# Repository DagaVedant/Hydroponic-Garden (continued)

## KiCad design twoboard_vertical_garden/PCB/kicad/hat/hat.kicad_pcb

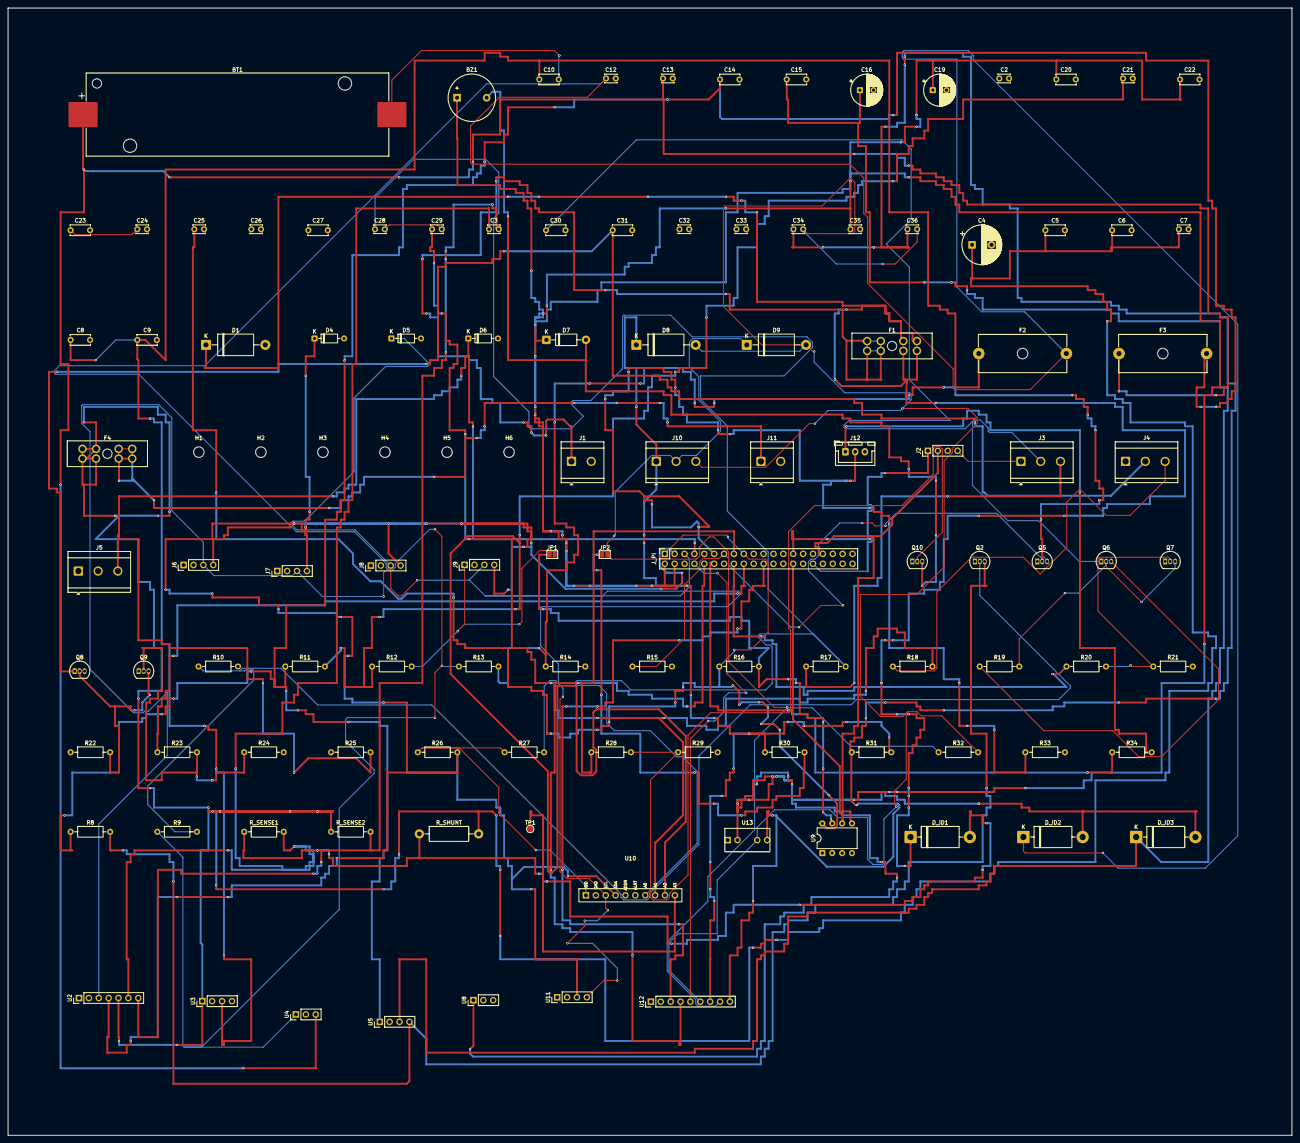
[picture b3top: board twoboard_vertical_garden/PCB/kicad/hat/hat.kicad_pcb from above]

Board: 4 copper layers, 330.0 x 289.7 mm, 117 parts (0 on the bottom side), 56 nets.

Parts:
BT1: 18650 protected; BatteryHolder_Keystone_1042_1x18650
BZ1: active 5V; Buzzer_12x9.5RM7.6
C2, C3, C7, C21, C24, C25, C26, C28, C29, C32, C33, C34: 100n; C_Disc_D3.0mm_W2.0mm_P2.50mm
C4: 470u 25V; CP_Radial_D10.0mm_P5.00mm
C5, C6: 10u 25V; C_Disc_D5.0mm_W2.5mm_P5.00mm
C8, C9, C10, C14, C15, C20, C23: 22u 10V; C_Disc_D5.0mm_W2.5mm_P5.00mm
C12, C13, C35, C36: 4u7; C_Disc_D3.0mm_W2.0mm_P2.50mm
C16: 220u 10V; CP_Radial_D8.0mm_P3.50mm
C19: 470u 10V; CP_Radial_D8.0mm_P3.50mm
C22, C27, C30, C31: 10u; C_Disc_D5.0mm_W2.5mm_P5.00mm
D1: SMBJ15A; D_DO-201AE_P15.24mm_Horizontal
D4, D5, D6: SMF5.0A; D_DO-35_SOD27_P7.62mm_Horizontal
D7: SS14; D_DO-41_SOD81_P10.16mm_Horizontal
D8, D9: SMAJ6.5CA; D_DO-201AE_P15.24mm_Horizontal
D_ID1, D_ID2, D_ID3: SB5H100; D_DO-201AD_P15.24mm_Horizontal
F1: 10A blade; FuseHolder_Blade_ATO_Littelfuse_FLR_178.6165
F2, F3: 3A; Fuseholder_Cylinder-5x20mm_Schurter_0031_8201_Horizontal_Op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
F4: 7.5A blade; FuseHolder_Blade_ATO_Littelfuse_FLR_178.6165
H1, H2, H3, H4, H5, H6: M2.5; MountingHole_2.7mm_M2.5
J1: 12V IN; TerminalBlock_CUI_TB007-508-02_1x02_P5.08mm_Horizontal
J2: spare gpio; PinHeader_1x04_P2.54mm_Vertical
J3: pH board; Gravity_TB3
J4: EC board; Gravity_TB3
J5: DS18B20; TerminalBlock_CUI_TB007-508-03_1x03_P5.08mm_Horizontal
J6: sht31 module; PinHeader_1x04_P2.54mm_Vertical
J7: veml7700 module; PinHeader_1x04_P2.54mm_Vertical
J8: scd40 module; PinHeader_1x04_P2.54mm_Vertical
J9: oled ssd1306; PinHeader_1x04_P2.54mm_Vertical
J10: RS485 A B G; TerminalBlock_CUI_TB007-508-03_1x03_P5.08mm_Horizontal
J11: 12V OUT; TerminalBlock_CUI_TB007-508-02_1x02_P5.08mm_Horizontal
J12: HB FLT GND; JST_XH_B3B-XH-A_1x03_P2.50mm_Vertical
JP1: WP; SolderJumper-2_P1.3mm_Open_Pad1.0x1.5mm
JP2: term; SolderJumper-2_P1.3mm_Open_Pad1.0x1.5mm
J_PI: Pi 40 pin; PinSocket_2x20_P2.54mm_Vertical
Q2, Q5, Q7, Q9, Q10: 2N7002; TO-92_Inline
Q6, Q8: AO3401A; TO-92_Inline
R8, R9, R10, R11, R12, R13, R14, R21, R24, R29: 100k; R_Axial_DIN0207_L6.3mm_D2.5mm_P10.16mm_Horizontal
R15, R16, R19, R22, R33: 10k; R_Axial_DIN0207_L6.3mm_D2.5mm_P10.16mm_Horizontal
R17, R18, R20, R23, R28: 1k; R_Axial_DIN0207_L6.3mm_D2.5mm_P10.16mm_Horizontal
R25: 4k7; R_Axial_DIN0207_L6.3mm_D2.5mm_P10.16mm_Horizontal
R26, R27: 2k2; R_Axial_DIN0207_L6.3mm_D2.5mm_P10.16mm_Horizontal
R30: 120R; R_Axial_DIN0207_L6.3mm_D2.5mm_P10.16mm_Horizontal
R31, R32: 47k; R_Axial_DIN0207_L6.3mm_D2.5mm_P10.16mm_Horizontal
R34: 100R; R_Axial_DIN0207_L6.3mm_D2.5mm_P10.16mm_Horizontal
R_SENSE1, R_SENSE2: 10R; R_Axial_DIN0207_L6.3mm_D2.5mm_P10.16mm_Horizontal
R_SHUNT: 5m 2512; R_Axial_DIN0411_L9.9mm_D3.6mm_P15.24mm_Horizontal
TP1: AIN3; TestPoint_Pad_D1.5mm
U2: INA226 module 0x40; PinHeader_1x07_P2.54mm_Vertical
U3: buck module 12V->5V; PinHeader_1x04_P2.54mm_Vertical
U4: li-ion charger module (500mA); PinHeader_1x03_P2.54mm_Vertical
U5: XL6009 boost module (VBAT_F->5V); PinHeader_1x04_P2.54mm_Vertical
U8: AMS1117 3.3V module; PinHeader_1x03_P2.54mm_Vertical
U9: 24LC32A; DIP-8_W7.62mm
U10: ADS1115 module; ADS1115_Module
U11: DS3231 RTC module; PinHeader_1x04_P2.54mm_Vertical
U12: isolated RS485 module; PinHeader_1x09_P2.54mm_Vertical
U13: B0505S-1WR3; B0505S_SIP4

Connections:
12V_FUSED: D1.1, D_ID1.1, F1.2
+3V3: C2.1, C23.1, C24.1, C26.1, C27.1, C32.1, C33.1, J2.3, J5.1, J6.1, J7.1, J8.1, J9.2, Q6.3, Q8.3, R15.2, R19.1, R22.1, R25.1, R26.1, R27.1, R33.2, U2.2, U8.3, U10.8, U11.1, U12.1
+3V3_PI: C25.1, J_PI.1, J_PI.17, R16.1, U9.8
+5V: BZ1.1, C19.1, C20.1, C22.1, C35.1, D7.1, D_ID2.2, D_ID3.2, J_PI.2, J_PI.4, U8.1, U13.2
+5VISO: C34.1, C36.1, R31.1, U12.9, U13.4
+5V_BAT: C15.1, C16.1, D_ID3.1, U5.3
+5V_IN: C8.1, C9.1, C10.1, F2.1, U3.3
+5V_MAINS: C12.1, D_ID2.1, F2.2, R9.1, R13.1, U4.1
+12V: C4.1, C5.1, C6.1, C7.1, F4.1, R_SENSE2.1, R_SHUNT.2, U2.5, U3.1
+12V_IN: F1.1, J1.1
/12V_DIODE: D_ID1.2, R_SENSE1.1, R_SHUNT.1
/AIN3: TP1.1, U10.7
/BUZZ: J_PI.15, R28.1
/EC_ADC: C29.1, R18.2, U10.5
/EC_EN: J_PI.18, R23.1
/FLT: J12.2, J_PI.11, R33.1
/HB: J_PI.12, R34.1
/INA_INP: C3.1, R_SENSE1.2, U2.6
/MAINS_N: J_PI.13, Q5.3, R15.1
/PH_ADC: C28.1, R17.2, U10.4
/PH_EN: J_PI.16, R20.1
/RS485_DE: J_PI.22, U12.3
/RS485_RX: J_PI.10, U12.4
/RS485_TX: J_PI.8, U12.5
/SCL: D5.1, J6.3, J7.3, J8.3, J9.3, J_PI.5, R27.2, U2.3, U10.10, U11.4
/SDA: D4.1, J6.4, J7.4, J8.4, J9.4, J_PI.3, R26.2, U2.4, U10.9, U11.3
/VBAT_SENSE: C21.1, R11.2, R12.1, U10.6
/W1: D6.1, J5.3, J_PI.7, R25.2
EC_VCC: C31.1, J4.1, Q8.1
GND: BT1.2, C2.2, C4.2, C5.2, C6.2, C7.2, C8.2, C9.2, C10.2, C12.2, C13.2, C14.2, C15.2, C16.2, C19.2, C20.2, C21.2, C22.2, C23.2, C24.2, C25.2, C26.2, C27.2, C28.2, C29.2, C30.2, C31.2, C32.2, C33.2, C35.2, D1.2, D4.2, D5.2, D6.2, J1.2, J2.4, J3.2, J4.2, J5.2, J6.2, J7.2, J8.2, J9.1, J11.2, J12.3, JP1.2, J_PI.6, J_PI.9, J_PI.14, J_PI.20, J_PI.25, J_PI.30, J_PI.34, J_PI.39, Q2.1, Q5.1, Q7.1, Q9.1, Q10.1, R10.2, R12.2, R14.2, R21.2, R24.2, R29.2, U2.1, U3.2, U3.4, U4.2, U5.2, U8.2, U9.1, U9.2, U9.3, U9.4, U10.1, U10.3, U11.2, U12.2, U13.1
GNDISO: C34.2, C36.2, D8.2, D9.2, J10.3, R32.2, U12.6, U13.3
unnamed: BZ1.2, D7.2, Q10.3
unnamed: D8.1, J10.1, R30.1, R31.2, U12.7
unnamed: D9.1, J10.2, JP2.2, R32.1, U12.8
unnamed: J2.1, J_PI.32
unnamed: J2.2, J_PI.33
unnamed: J3.3, R17.1
unnamed: J4.3, R18.1
unnamed: F4.2, J11.1
unnamed: J12.1, R34.2
unnamed: JP1.1, R16.2, U9.7
unnamed: JP2.1, R30.2
unnamed: J_PI.27, U9.5
unnamed: J_PI.28, U9.6
unnamed: Q2.3, R8.2, U5.4
unnamed: Q2.2, R9.2, R10.1
unnamed: Q5.2, R13.2, R14.1
unnamed: Q6.2, Q7.3, R19.2
unnamed: Q7.2, R20.2, R21.1
unnamed: Q8.2, Q9.3, R22.2
unnamed: Q9.2, R23.2, R24.1
unnamed: Q10.2, R28.2, R29.1
unnamed: C3.2, R_SENSE2.2, U2.7
PH_VCC: C30.1, J3.1, Q6.1
VBAT: BT1.1, C13.1, F3.1, U4.3
VBAT_F: C14.1, F3.2, R8.1, R11.1, U5.1

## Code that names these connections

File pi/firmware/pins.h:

// the pumps board, rev d. one line per pico pin, same names as the schematic.
#pragma once

#define PIN_LED_PWM_N    0   // led strip gate driver, inverted: a high here turns the strip off
#define PIN_PUMP1_EN     2   // micro
#define PIN_PUMP2_EN     3   // gro
#define PIN_PUMP3_EN     4   // ph down
#define PIN_HB_ALIVE     5   // the monostable's Q: high while the pi keeps sending
#define PIN_FLOW         6   // yf-s201 pulses, buffered
#define PIN_SONAR_TRIG   7
#define PIN_SONAR_ECHO   8   // through the 2k2 / 3k3 divider
#define PIN_FAN_PWM      9
#define PIN_FAN_TACH    10
#define PIN_FLT_DRV     11   // open drain to the pi through a 2n7002: high here pulls FLT low
#define PIN_HB_IN       12   // the pi's heartbeat line, which carries the command frames
#define PIN_ARM         13   // and-ed with HB_ALIVE in hardware to switch the dosing rail
#define PIN_LED_RAIL    14
#define PIN_LED_PUMP    15
#define PIN_LED_LINK    16
#define PIN_SDA         20
#define PIN_SCL         21
#define PIN_LED_ISENSE  26   // adc0: ina180a2 (x50) over 10 mohm, 0.5 v per amp
#define PIN_RAIL_SENSE  27   // adc1: 12 v rail through 10k / 3k3

#define ADS1115_ADDR    0x49 // addr pin high. ain0..2 = pump 1..3 current, ina180a2 (x50) over 0.1 ohm, 5 v per amp

#define LINK_BAUD       9600
#define FRAME_TIMEOUT_MS 1000   // no valid frame for this long: pumps off, disarm
#define TELEMETRY_MS     250

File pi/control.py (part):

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LED_SHUNT_OHMS = 0.01                          # R22
INA226_SHUNT_OHMS = 0.005                      # R_SHUNT, the 12V input

PIN_PH_POWER = 23           # /PH_EN
PIN_EC_POWER = 24           # /EC_EN
PIN_FLOW = 17               # /FLOW, off the CD40106 schmitt buffer
PIN_FAN_TACH = 27           # /FAN_TACH
PIN_HB_ALIVE = 18           # /HB_ALIVE -- the watchdog retrigger. see Watchdog below
PIN_ARM = 25                # /ARM -- the software's own deliberate arm/disarm

# the CD4538 monostable's timeout, measured off the real board: R1=470k, C2=10uF
# on MONO_RC/MONO_CEXT. CD4538 timeout ~= 0.7 * R * C -- verify on the bench, this
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

class PulseCounter:
    """A GPIO edge counter for anything that outputs pulses: the flow sensor and
    the fan tachometer are both this, just with different pulses-per-unit."""

    def __init__(self, pin: int, simulate: bool = False, sim_hz: float = 0.0) -> None:
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        super().__init__(simulate)
        self.interval_s = interval_s
        self._last_ts = time.time()
        self.flow = PulseCounter(PIN_FLOW, simulate, sim_hz=0.0)
        self.fan = PulseCounter(PIN_FAN_TACH, simulate, sim_hz=(FAN_DUTY * 2400.0 / 60.0 * 2))

    def read(self) -> List[Reading]:
        now = time.time()
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        self._thread: Optional[threading.Thread] = None
        if not simulate:
            from gpiozero import DigitalOutputDevice
            self._hb = DigitalOutputDevice(PIN_HB_ALIVE, initial_value=False)
            self._arm = DigitalOutputDevice(PIN_ARM, initial_value=False)  # disarmed until start()

    def start(self) -> None:
        if self.simulate:
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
